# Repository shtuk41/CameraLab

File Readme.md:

# ESP32 Command & Setup Reference

A comprehensive collection of essential commands, environment paths, permission fixes, and workflow steps for ESP32 development with ESP-IDF.

---

## 1. Environment Initialization

Initialize the ESP-IDF environment variables in your current terminal session:

```bash
. /home/aleksander/.espressif/v6.1-beta1/esp-idf/export.sh
```

---

## 2. Project Target & Dependencies

### Set Target Hardware
Configure the project target for a specific microcontroller (e.g., ESP32-S3):
```bash
idf.py set-target esp32s3
```

### Add Component Dependencies
Add external components or libraries from the ESP Component Registry (e.g., the ESP32 camera driver):
```bash
idf.py add-dependency "espressif/esp32-camera"
```

### Reconfigure Project
Regenerate CMake files and apply dependency updates:
```bash
idf.py reconfigure
```

---

## 3. Build & Flash Workflows

### Build Firmware
Compile the project:
```bash
idf.py build
```

### Flash Firmware
Upload the compiled binary to your board (replace `/dev/your_actual_port` with your device port, such as `/dev/ttyUSB0` or `/dev/ttyACM0`):
```bash
idf.py -p /dev/your_actual_port flash
```

---

## 4. Port Discovery & Permissions

### Find Connected Devices
List all available USB/UART serial ports connected to the system:
```bash
ls -l /dev/tty[UA]*
```

### Grant Temporary Port Access
Quickly grant read/write permissions to a specific serial port if permission is denied:
```bash
sudo chmod a+rw /dev/ttyUSB0
# or for ACM devices:
sudo chmod a+rw /dev/ttyACM0
```

### Permanent Permission Setup (Dialout & Plugdev)
Add your user to the `dialout` and `plugdev` groups to access serial ports permanently without using `sudo` (requires a system logout/login or reboot to take effect):
```bash
sudo usermod -aG dialout,plugdev $USER

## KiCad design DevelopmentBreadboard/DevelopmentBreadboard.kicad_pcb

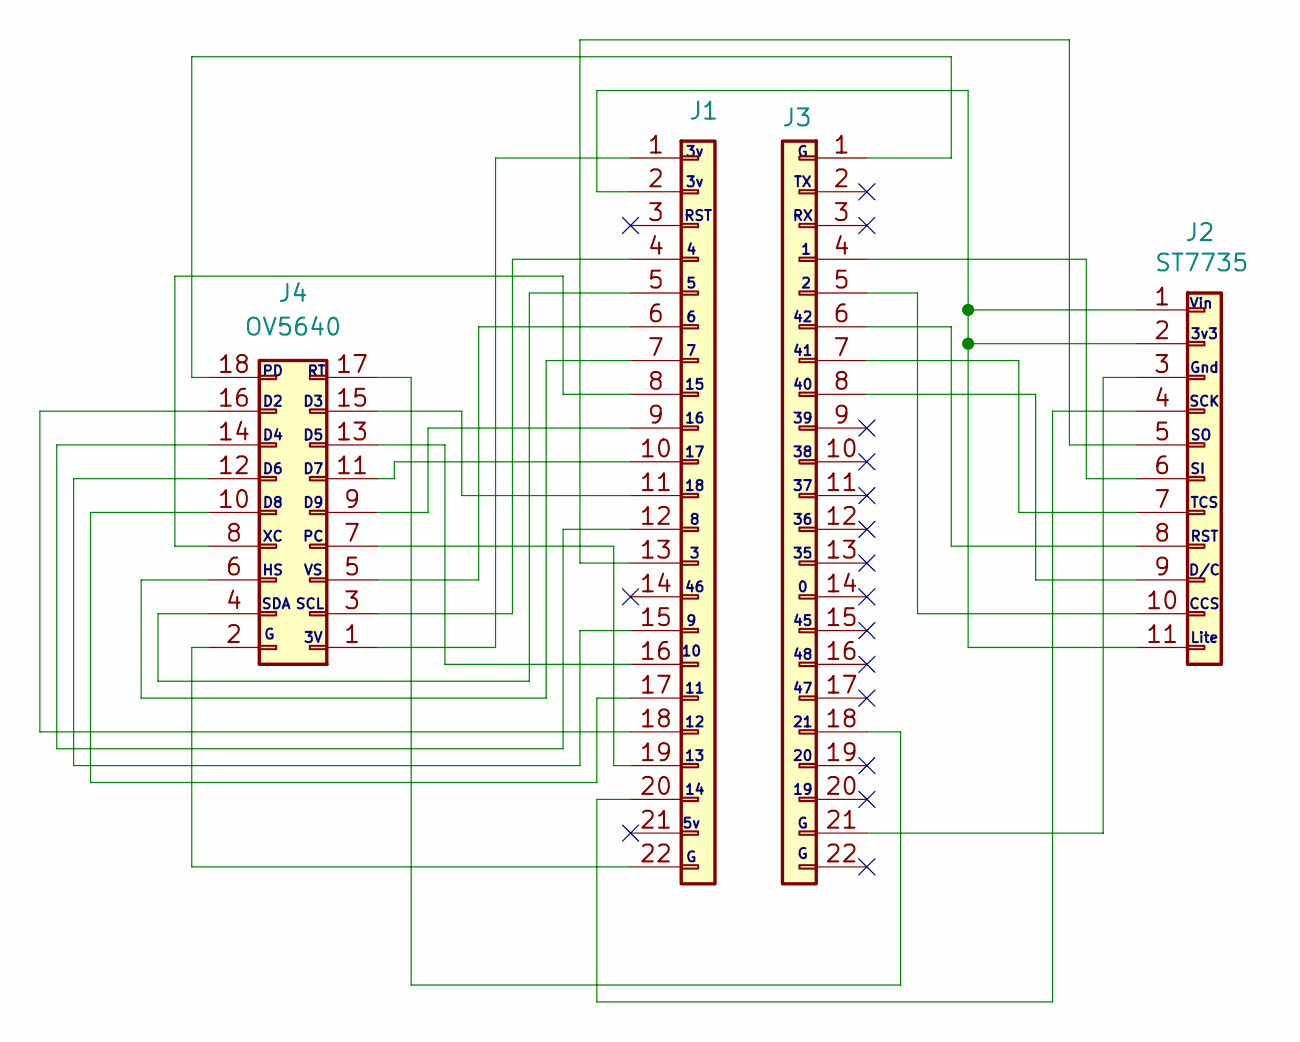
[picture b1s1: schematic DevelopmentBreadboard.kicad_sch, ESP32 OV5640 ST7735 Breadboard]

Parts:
J1, J3: Conn_01x22; PinSocket_1x22_P2.54mm_Vertical
J2: ST7735; PinSocket_1x11_P2.54mm_Vertical
J4: OV5640; PinSocket_2x09_P2.54mm_Vertical

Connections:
unnamed: J1.1, J4.1
unnamed: J1.2, J2.1, J2.2, J2.11
unnamed: J1.4, J4.3
unnamed: J1.5, J4.4
unnamed: J1.6, J4.5
unnamed: J1.7, J4.6
unnamed: J1.8, J4.8
unnamed: J1.9, J4.9
unnamed: J1.10, J4.11
unnamed: J1.11, J4.15
unnamed: J1.12, J4.14
unnamed: J1.13, J2.5
unnamed: J1.15, J4.12
unnamed: J1.16, J4.13
unnamed: J1.17, J4.10
unnamed: J1.18, J4.16
unnamed: J1.19, J4.7
unnamed: J1.20, J2.4
unnamed: J1.22, J4.2
unnamed: J2.3, J3.21
unnamed: J2.6, J3.4
unnamed: J2.7, J3.7
unnamed: J2.8, J3.6
unnamed: J2.9, J3.8
unnamed: J2.10, J3.5
unnamed: J3.1, J4.18
unnamed: J3.18, J4.17

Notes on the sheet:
SCK
CCS
Gnd
Lite
SDA
RST
3v3
Vin
D/C
TCS
SCL

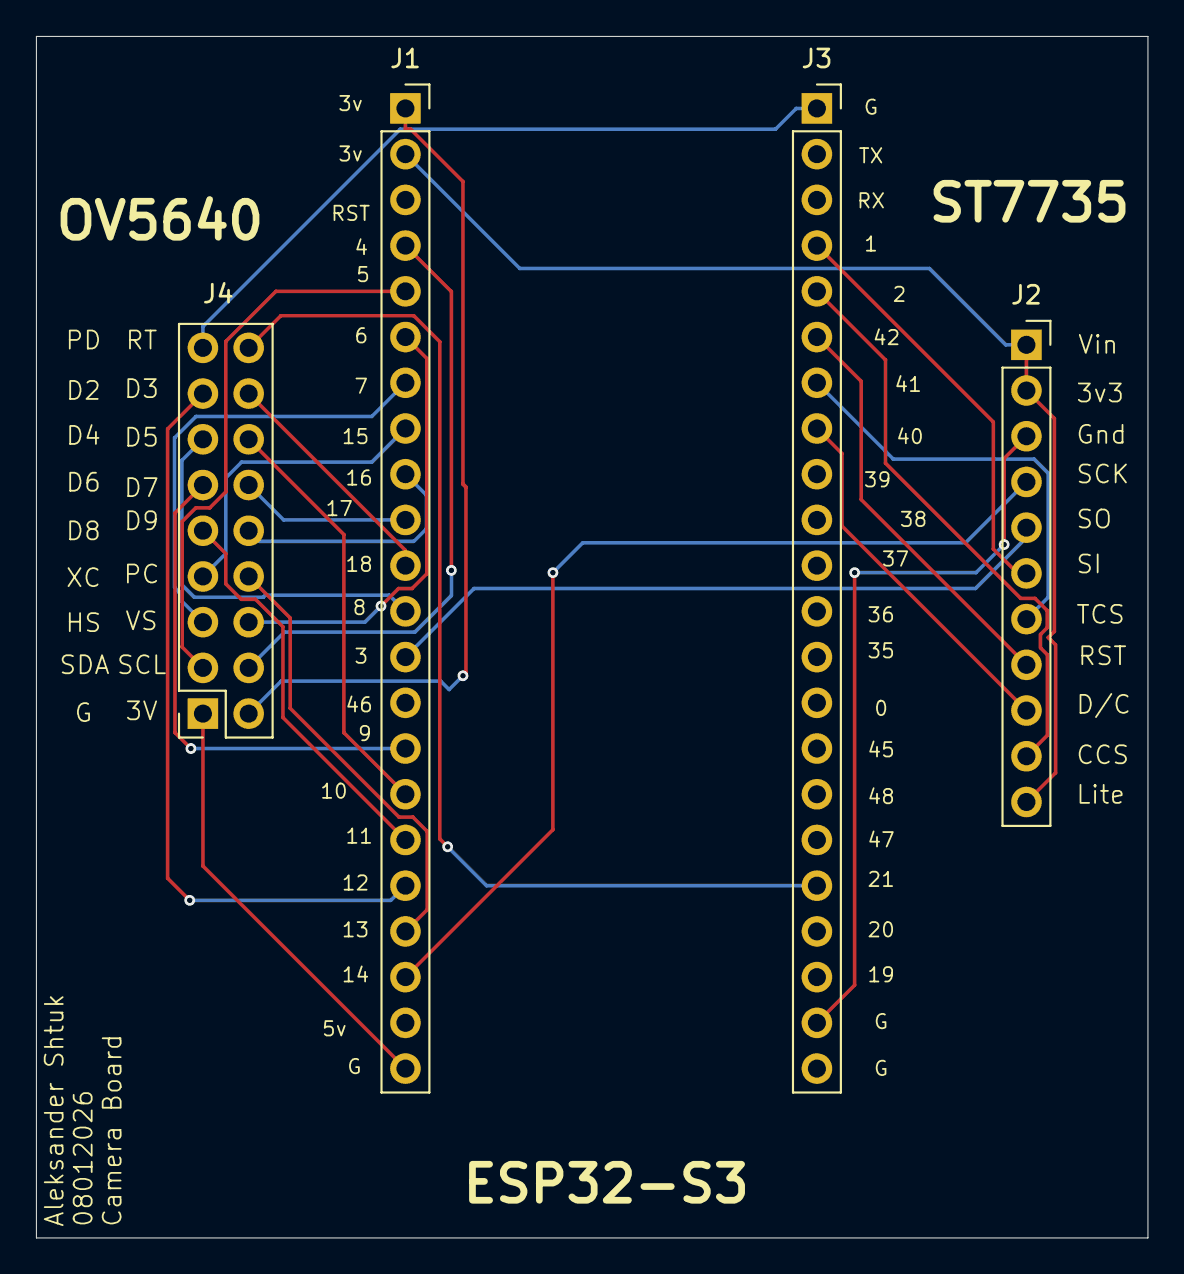
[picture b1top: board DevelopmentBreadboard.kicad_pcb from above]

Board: 2 copper layers, 61.8 x 66.8 mm, 4 parts (0 on the bottom side), 27 nets.
